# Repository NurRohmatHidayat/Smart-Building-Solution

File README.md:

# GriyaTech
## Smart-Building-System-Berbasis IoT

Proyek ini bertujuan untuk mengembangkan sistem automasi cerdas berbasis IoT untuk Smart Building, menggunakan komponen utama seperti ESP32, RTC, dan berbagai sensor. ESP32 bertindak sebagai mikroprosesor utama yang mengontrol komunikasi antar sensor dan perangkat, memungkinkan pemantauan dan pengontrolan secara real-time melalui jaringan Wi-Fi. Sistem ini dilengkapi dengan RTC (Real-Time Clock) untuk menjaga sinkronisasi waktu, serta sensor suhu DHT11 yang digunakan untuk mengoptimalkan pengaturan suhu dan kelembaban di dalam gedung.

Untuk memantau konsumsi energi, digunakan sensor arus ACS712 dan sensor tegangan ZMPT101B yang secara akurat mengukur penggunaan listrik dan tegangan pada berbagai perangkat. Selain itu, Relay SPDT (3A 3,3V) berfungsi sebagai saklar otomatis yang memungkinkan pengendalian perangkat elektronik seperti lampu dan sistem pendingin. 

Dengan bantuan teknologi IoT, seluruh data dari sensor-sensor ini dikirimkan ke platform cloud, memungkinkan pemilik gedung untuk memantau penggunaan energi dan kondisi lingkungan secara langsung dari aplikasi mobile. Sistem ini dirancang untuk meningkatkan efisiensi energi, kenyamanan, serta keamanan penghuni gedung dengan mengotomatiskan berbagai fungsi dan memberikan kendali yang lebih fleksibel.

## Support By :
>- Dosen Pengampu : Akhmad Hendriawan ST., MT. (NIP.197501272002121003)
>- Mata kuliah : IoT dan Jaringan Sensor
>- Program Studi : D4 Teknik Elektronika
>- Politeknik Elektronika Negeri Surabaya<br>

## Team Member :
|      NRP      |       Nama      |    Jobdesk    |   Akun |
| :-----------:|:----------------:| :------------:| :-----:|
| 2122600003    | Raditya Giananta  | Hardware Developer       | [Radit](https://github.com/Raditya-G)
| 2122600006    | Nataratungga Xina T         |   UI/UX Designer | [Ratu](https://github.com/nataratungga)
| 2122600007    | Bisma Arya Putra         |    Programmer      | [Bisma](https://github.com/Bismaap)
| 2122600012    | Nur Rohmat Hidayat                | Project Manager | [Rohmat](https://github.com/NurRohmatHidayat)
| 2122600020    | Ezar Prasetya               | UI/UX Designer     | [Ezar](https://github.com/EzarPrasetya)
| 2122600030    | Ziyad Nur Muhammad               | 3D Designer     |[Ziyad](https://github.com/Yadnur)

#### Preview Video Produk

https://github.com/user-attachments/assets/8750dca7-19aa-41fc-97a8-4954fc9a0d99

#### Preview Video Iklan 

https://github.com/user-attachments/assets/dadaf9dd-aac7-4402-b66a-3c4db6aee498

#### Preview Slide Presentasi

- [Slide Presentasi PDF](https://github.com/NurRohmatHidayat/Smart-Building-Solution/tree/main/Assets)

## Daftar Isi
- [Komponen Yang Digunakan](#Komponen-Yang-Digunakan)
- [Wiring Plan](#Wiring-Plan)
- [Hardware](#Hardware)
- [Desain 3D](#Desain-3D)
- [Program ESP32](#Program-ESP32)
- [Program Design UI/UX](#Pogram-Design-UI/UX)

## Komponen Yang Digunakan
1. **Hardware**<br>
    a. ESP32<br>
    b. Shield PCB<br>
    c. RTC<br>
    d. Sensor Suhu DHT11<br>
    e. Sensor Arus ACS712<br>
    f. Sensor Tegangan (ZMPT101B)<br>
    g. Relay SPDT (3A 3,3V)<br>

2. **Software**<br>
    a. Arduino ide<br>
    b. KiCad<br>
    c. Inventor<br>
    d. Visual Studio Code (VSC)<br>
    e. Eagle<br>

3. **Alat**<br>
    a. Solder<br>
    b. Timah solder<br>
    c. Kabel jumper<br>
    d. Breadboard<br>
    e. Obeng<br>
 
## Wiring Plan
>- First Floor Plan
>- 
>- Second Floor Plan
>- 

## Link YouTube 

Link youtube video produk
https://youtu.be/4Z63st0WbLA

Link youtube video iklan
https://youtu.be/mOYy9-KewV4

## [Hardware](https://github.com/NurRohmatHidayat/Smart-Building-Solution/tree/main/Hardware)

Berikut ini adalah hasil skematik rangkaian Smart Building System IoT menggunakan software KiCad.
<div align="center">

</div>

Berikut ini adalah hasil 3D dari  rangkaian Smart Building System IoT menggunakan software KiCad.
<div align="center">

</div>

Berikut ini adalah hasil 3D dari  rangkaian Smart Building System IoT menggunakan software KiCad.
<div align="center">

</div>

## [Desain 3D](https://github.com/NurRohmatHidayat/Smart-Building-Solution/tree/main/Desain%203D)

## Preview Video 3D Design

https://github.com/user-attachments/assets/e34dfbfa-0edd-4161-8904-f4dbc712b04a

Berikut adalah Link Thingivers Design 3D. Asset 3D bisa didownload pada link [Thingivers](https://www.thingiverse.com/thing:6796394)

## Diagram Block

## Diagram Arsitektur System
Berikut adalah alur Diagram untuk mengirim data sensor dari publisher ke database

## Preview Penggunaan OTA

<div align="center">

</div>

## Program ESP32

Program utama dari projek ini :
- [Arduino dengan C](https://github.com/NurRohmatHidayat/Smart-Building-Solution/tree/main/Program%20ESP32/Smart%20Building/Smart%20Building/src)

Berikut adalah video demontrasi prototype hardware. 

https://github.com/user-attachments/assets/7abacf07-8daf-47ce-86e2-667d23beedc0

Simulasi ini kami menggunakan ESP32 untuk mengontrol sensor dan modul yang terhubung di breadboard. Simulasi dilakukan menggunakan Wokwi, yang memudahkan pengujian rangkaian secara virtual sebelum implementasi fisik. Rangkaian melibatkan sensor DHT11, modul relay, LED indikator, potensiometer, dan RTC untuk sinkronisasi waktu.

Relay digunakan untuk mengontrol perangkat eksternal, sementara LED menunjukkan status sistem. Simulasi ini membantu dalam debugging dan memastikan komunikasi antar komponen berjalan baik. Meskipun Wokwi tidak menyediakan semua komponen, platform ini sangat berguna untuk pengujian dan visualisasi fungsi dasar rangkaian, membantu mengidentifikasi masalah sebelum produksi fisik.

Berikut adalah video demontrasi alat menggunakan wokwi. Klik link [Video Simulasi Software](https://youtu.be/oXDYyiHHBaU "Video Simulasi Software")

## [Alur Komunikasi]

Pada proyek ini, ESP32 menggunakan Wi-Fi Manager untuk mempermudah proses koneksi ke jaringan Wi-Fi. Wi-Fi Manager memungkinkan pengguna untuk memilih dan menghubungkan ESP32 ke jaringan internet tanpa harus mengubah kode sumber setiap kali ada perubahan pada jaringan.
Berikut tampilan pada wifi manager untuk menghubungkan ESP32 ke jaringan internet

<div align="center">

</div>

Setelah ESP32 terhubung ke internet, modul ini akan mengirim data secara berkala ke broker MQTT (dalam hal ini menggunakan broker Cool MQTT). Broker MQTT berfungsi sebagai perantara yang memungkinkan ESP32 mengirim data ke sistem lain dalam arsitektur ini.
berikut tampilan broker.mqtt.cool yang menerima data sensor dari publisher ESP32

Node-RED digunakan sebagai back end untuk proyek web kami, yang berfungsi mengelola aliran data dan pemrosesannya. Data yang ditampilkan pada antarmuka web berasal dari broker MQTT di mqtt.cool, di mana Node-RED berlangganan ke topik yang relevan, memproses data sesuai kebutuhan, dan menyajikannya ke front end. Pengaturan ini memungkinkan penanganan data secara real-time dan integrasi yang efisien dengan platform web kami.

Berikut adalah alur dari program Node Red yang berfungsi untuk menerima data mqtt.cool kemudian disimpan pada database Mysql.

Berikut ini adalah program untuk Back-end Smart Building System IoT menggunakan Node-RED [Node-RED](https://github.com/NurRohmatHidayat/Smart-Building-Solution/tree/main/UI/UX%20Designer)

Berikut ini adalah program untuk WEB Smart Building System IoT menggunakan bahasa HTML [Program](https://github.com/NurRohmatHidayat/Smart-Building-Solution/tree/main/UI/UX%20Designer/node-red)

## Design Protitype Figma

<div align="center">

</div>

## [Langkah-Langkah Penggunaan]
Berikut adalah langkah-langkah menggunakan produk "smart building" untuk para pelanggan:

1. Mengaktifkan Perangkat
  -Pastikan perangkat sudah terisi daya atau menggunakan baterai bawaan.
  -Tekan tombol Power untuk menghidupkan perangkat. Indikator lampu akan menyala sebagai tanda bahwa perangkat aktif.

2. Menghubungkan Perangkat ke Wi-Fi
  -Setelah perangkat aktif, buka smartphone atau laptop Anda.
  -Cari jaringan Wi-Fi dengan nama (ESP32_AP) sesuai perangkat, misalnya: SmartBuilding-Setup.
  -Hubungkan perangkat Anda ke Wi-Fi tersebut.
  -Secara otomatis, halaman konfigurasi Wi-Fi Manager akan terbuka. Jika tidak terbuka, buka browser dan masukkan alamat IP: 192.168.4.1.
  -Pada halaman Wi-Fi Manager:
     Pilih jaringan Wi-Fi gedung Anda.
     Masukkan kata sandi Wi-Fi.
     Klik Connect.
  -Tunggu hingga perangkat terhubung ke internet. Indikator lampu hijau akan menyala jika koneksi berhasil.

3. Memastikan Perangkat Aktif dan Berfungsi
  -Perangkat akan mulai membaca data seperti tegangan, arus, daya listrik, dan suhu ruangan.
  -Pastikan semua sensor bekerja dengan benar dengan melihat indikator status pada perangkat.

4. Mengakses Web untuk Memantau Data Sensor
  -Buka browser Anda dan masukkan alamat web yang telah diberikan, misalnya: [http://d4elkasmartbuilding.rf.gd/?i=1] atau IP tertentu.
  -Masuk ke dashboard menggunakan kredensial yang sudah disediakan.

5. Mengelola dan Memantau Data
  -Pada dashboard web, Anda dapat:
  -Melihat Data Real-Time: Tegangan, arus, daya, dan suhu.
  -Mengontrol Perangkat: Atur suhu ruangan dengan AC atau kipas.
  -Jadwalkan Lampu: Tentukan kapan lampu dinyalakan/dimatikan.
  -Semua perubahan yang Anda lakukan akan langsung diterapkan pada perangkat.

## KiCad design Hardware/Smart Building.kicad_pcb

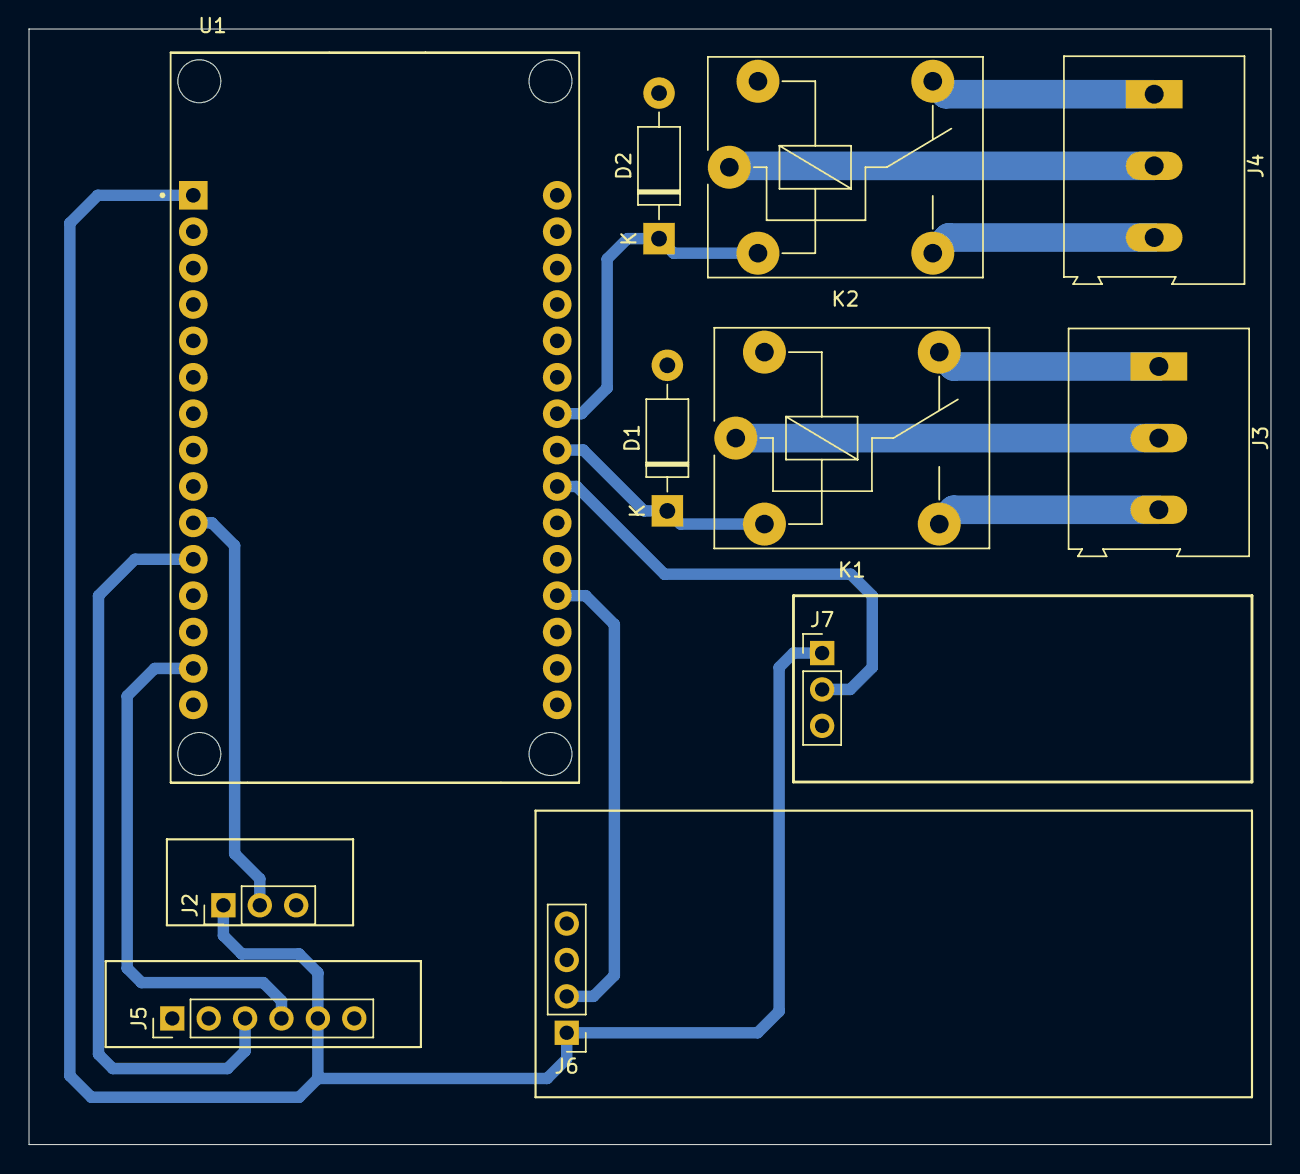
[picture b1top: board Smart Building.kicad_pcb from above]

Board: 2 copper layers, 86.7 x 77.9 mm, 11 parts (0 on the bottom side), 15 nets.

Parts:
D1, D2: 1N4001; D_DO-41_SOD81_P10.16mm_Horizontal
J2: DHT11; PinHeader_1x03_P2.54mm_Vertical
J3, J4: Screw_Terminal_01x03; TerminalBlock_Altech_AK300-3_P5.00mm
J5: Conn_01x06_Pin; PinHeader_1x06_P2.54mm_Vertical
J6: ZMPT101b; PinHeader_1x04_P2.54mm_Vertical
J7: ACS712; PinHeader_1x03_P2.54mm_Vertical
K1, K2: Relay_SPDT; Relay_SPDT_Finder_36.11
U1: ESP32-DEVKIT-V1; MODULE_ESP32_DEVKIT_V1

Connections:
+3.3V: J2.1, J5.5, J6.1, J7.1, U1.1 (3V3)
D25: D1.1 (K), K1.A1, U1.23 (D25)
D26: D2.1 (K), K2.A1, U1.24 (D26)
D33: J7.2, U1.22 (D33)
D34: J6.2, U1.19 (D34)
DHT11: J2.2, U1.10 (D19)
GND: D1.2 (A), D2.2 (A), J2.3, J5.6, J6.3, J6.4, J7.3, K1.A2, K2.A2, U1.2 (GND), U1.29 (GND)
unnamed: J3.1, K1.12
unnamed: J3.2, K1.11
unnamed: J3.3, K1.14
unnamed: J4.1, K2.12
unnamed: J4.2, K2.11
unnamed: J4.3, K2.14
SCL: J5.4, U1.14 (D22)
SDA: J5.3, U1.11 (D21)

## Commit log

2024-10-08 ganti
2024-10-08 Mengubah Logo
2024-10-08 penambahan readme
2024-10-08 adding folder
2024-10-08 Rangkaian Modul pada Wokwi
    Rangkaian yang digunakan untuk simulasi modul ESP32
2024-10-09 add schematic and pcb board
2024-10-09 awal
2024-10-09 Finalisasi-Projek
2024-10-09 add program esp32
2024-10-09 README.md
2024-10-12 Menambahkan 2 Relay
    Menambahkan 2 Relay dan 2 LED untuk menggantikan AC dan lampu ruangan
2024-10-12 menambahkan 2 Relay
2024-10-13 menambahkan program untuk kedua relay
2024-10-13 Melengkapi kekurangan README.md
2024-10-13 update 3D Design
2024-10-13 Menambahkan program web
2024-10-20 adding hardware component in 3D Design and file 3D
2024-10-21 memperbarui schematic dan board dengan menambahkan switch dan connector untuk baterai
2024-10-24 Update link to the Thinginvers
2024-10-28 Upload Logo Typhography
2024-10-28 Menambah Foto
2024-10-28 memperbarui rangkaian chematic dan board dengan menambahkan sensor tegangan baterai
2024-10-28 mengubah program web
2024-10-28 menambahkan program wifi manager
2024-10-28 Update README.md
    update akun github atas nama Raditya Giananta dengan username "Raditya-G" karena akun github yang lama dengan username "Radit-Gi" terkena suspended
2024-10-28 Mengganti program web
2024-10-29 memperbarui rangkaian chematic dan board dengan menambahkan opto coupler pc817 untuk mengaktifkan relay yang membutuhkan supply 5v
2024-11-07 merapihkan gambar yang ada pada readme
2024-11-07 menambahkan foder platform.io
2024-11-07 Menambahkan file Poster.jpg ke proyek
2024-11-08 Menambah Codingan
2024-11-08 Menambah Codingan Nodered
2024-11-08 memperbaiki branch
2024-11-08 Finalisasi projek (#32)
    * Update README.md
    * Melengkapi kekurangan README.md
    * Menambah Foto
    * Menambahkan file Poster.jpg ke proyek
    * Menambah Foto
    * Menambah Codingan
2024-11-09 menambahkan penjelasan tentang program node red pad readme
2024-11-09 Finalisasi projek (#34)
    * Update README.md
    * Melengkapi kekurangan README.md
    * Menambah Foto
    * Menambahkan file Poster.jpg ke proyek
    * Menambah Foto
    * Menambah Codingan
2024-11-09 Final (#36)
    * merapihkan gambar yang ada pada readme
    * menambahkan foder platform.io
    * memperbaiki branch
    * memperbaiki branch
2024-11-09 Menyimpan perubahan pada README.md
2024-11-09 Update File 3D Design Inventor
2024-11-10 Mengganti Poster
2024-11-10 memperbarui rangkaian schematic dan board dengan menambahkan opto coupler pc817 untuk mengaktifkan relay yang membutuhkan supply 5v
2024-11-10 Hardware (#38)
    * memperbarui schematic dan board dengan menambahkan switch dan connector untuk baterai
    * memperbarui schematic dan board dengan menambahkan switch dan connector untuk baterai
    * memperbarui rangkaian chematic dan board dengan menambahkan sensor tegangan baterai
    * memperbarui rangkaian chematic dan board dengan menambahkan opto coupler pc817 untuk mengaktifkan relay yang membutuhkan supply 5v
    * memperbarui rangkaian schematic dan board dengan menambahkan opto coupler pc817 untuk mengaktifkan relay yang membutuhkan supply 5v
    ---------
2024-11-10 Mengganti Poster terakhir bangettt
2024-11-10 Ratu (#40)
    * Mengganti Poster
    * Mengganti Poster terakhir bangettt
    ---------
2024-11-10 Add files via upload
    menambahkan gambar block diagram
2024-11-10 Update README.md
    menambahkan block diagram komunikasi untuk mengirim data sensor dari publisher ke database
2024-11-10 Update README.md
    update untuk alur komunikasi ke database
2024-11-10 Add files via upload
    menambahkan tampilan wifi manager
2024-11-10 Update README.md
    menambahkan deskripsi untuk menghubungkan esp32 ke jaringan internet menggunakan wifi manager
2024-11-10 Add files via upload
    menambahkan tampila wifi manager
2024-11-10 Update README.md
    memperbarui gambar tampilan wifi manager
2024-11-10 Update README.md
    menambahkan deskripsi proses kirim data sensor ke broker mqtt cool pada alur komunikasi
2024-11-10 Adding videos
2024-11-10 Menambahkan program untuk konek ke Firebase
2024-11-10 Menambahkan Link YouTube video GriyaTech.md
2024-11-11 Add files via upload
    menambahkan tampilan broker mqtt cool
2024-11-11 Update README.md
    menambahkan tampilan broker mqtt cool yang berhasil meneripa data sensor dari sensor dari publisher
2024-11-24 adding Block Diagram
2024-11-24 adding Block Diagram (#45)
2024-11-24 adding Code OTA for ESP32
2024-11-24 Menambahkan vidio iklan pada README.md
2024-11-24 Menambahkan link video ke youtube pada README.md
2024-11-25 Update README.md
    penambahan langkah-langkah penggunaan produk
2024-11-25 Update README.md
    update langkah penggunaan
2024-12-02 Adding Slide Presentasi
2024-12-02 Menambah foto Cetak 3D Print
2024-12-02 Adding Design Figma
2024-12-02 Update Presentasi
